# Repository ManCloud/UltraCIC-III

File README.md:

# UltraCIC-III
This code allows you to create a replacement CIC chip for N64 games that you own on an ATTiny25, ATTiny45 of ATTiny85. 
The original code was written by jesgdev and updated with multi-region support by saturnu. 
I simply extended the version Krikzz created under the name UltraCIC-II to support automatic switching between NTSC and PAL if the console was unable to boot.

# Instructions
- Install avra 
- Assemble the code
  - avra UltraCIC-III.asm -d {MCU}
  - {MCU} must be one of the supported MCUs (attiny25, attiny45 or attiny85)
- Flash the file to your ATTiny 
  - e.g.: "avrdude -p t25 -c usbtiny -U flash:w:UltraCIC-III.hex eeprom:w:UltraCIC-III.hex.eep" for attiny25
- Update fuses
  - e.g.: "avrdude -p t25 -c usbtiny -U lfuse:w:0xc0:m -U hfuse:w:0xdf:m" for attiny25
  
# More Information
[Sources for UltraCIC-II](https://web.archive.org/web/20180701050159/https://krikzz.com/pub/support/everdrive-64/ultracic2/)

[Multi-region patch information](https://krikzz.com/forum/index.php?topic=3450.0)

[Assembly guide by perkinsb1024](https://bitwise.bperki.com/2019/01/12/repairing-an-n64-cartridge-without-blowing-in-it/)

# PCB
see [pcb](pcb/) subfolder

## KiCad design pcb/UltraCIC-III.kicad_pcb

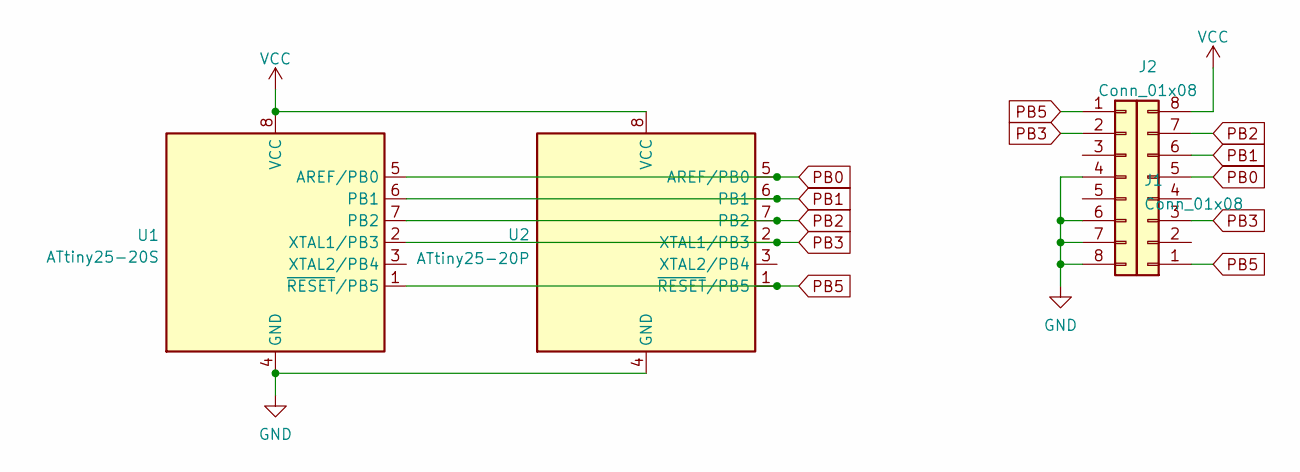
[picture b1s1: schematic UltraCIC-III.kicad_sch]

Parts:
J1, J2: Conn_01x08; PinHeader_1x08_P2.54mm_Vertical
U1: ATtiny25-20S; SOP-8-Wide
U2: ATtiny25-20P; DIP-8_W7.62mm

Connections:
GND: J1.4, J1.6, J1.7, J1.8, U1.4 (GND), U2.4 (GND)
PB0: J2.5, U1.5 (AREF/PB0), U2.5 (AREF/PB0)
PB1: J2.6, U1.6 (PB1), U2.6 (PB1)
PB2: J2.7, U1.7 (PB2), U2.7 (PB2)
PB3: J1.2, J2.3, U1.2 (XTAL1/PB3), U2.2 (XTAL1/PB3)
PB5: J1.1, J2.1, U1.1 (~RESET/PB5), U2.1 (~RESET/PB5)
VCC: J2.8, U1.8 (VCC), U2.8 (VCC)

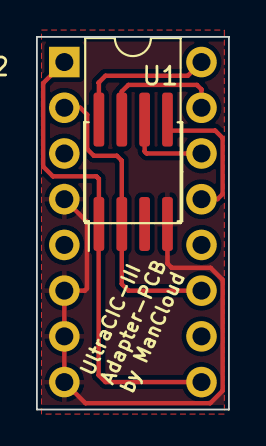
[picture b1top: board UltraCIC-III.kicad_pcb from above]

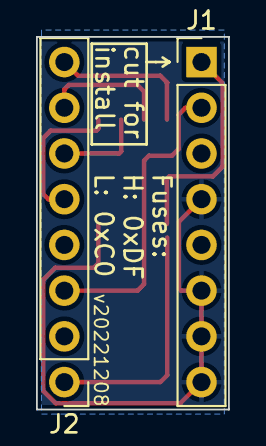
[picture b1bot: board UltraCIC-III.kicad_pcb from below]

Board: 2 copper layers, 10.7 x 20.7 mm, 4 parts (2 on the bottom side), 7 nets.

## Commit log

2020-07-28 Update UltraCIC-III.mk
    corrected fuses
2020-09-19 re-implemented CIC_TYPE
2022-11-06 Added PCB Design
2022-12-08 Updated PCB
